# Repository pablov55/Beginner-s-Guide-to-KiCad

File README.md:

# Beginner's Guide to KiCad
###### _by: Pablo Villamejor_

This tutorial will walk you through a simple KiCad example project from schematic building to PCB layout. In this project we will be given a schematic plan to follow and construct from scratch. We'll also touch on library linking, editing, and creation. We'll also export our PCB's necessary fabrication outputs so the board can be manufactured.

Now to begin we must first download and install KiCad. Head over to [the download page of the KiCad website,](https://www.kicad.org/download/) select your operating system, and download the most recent model.

>[!IMPORTANT]
This tutorial was written using KiCad 8.0 on Windows 10. (i.e. Use this version to follow along.)

Once you install and open KiCad, you can go to _File, New Project,_ and then name it whatever you like. Once named, you may select __Schematic Editor__ to begin.

## Creating the Schematic
When opened, the __Schematic Editor__ should appear like this, plain and empty besides the red border and text boxes.  

The objective of this project is to recreate this simple circuit and prepare it for manufacturing. The example has only 6 major components which will make this task more simple than most, but it is sufficient in order to understand the fundamental steps of KiCad and PCB design.

### Adding Symbols

To begin recreating this circuit, first add the components. This can be done using the _Add Symbols_ button on the right toolbar, or press the _"A"_ button on your keyboard, then left click anywhere on your workspace to begin selecting your component.

This will open up a window where you can input the name of the component you are trying to place. Most of the components have their names beside them (unless they were renamed, like is the case for the connectors in the example circuit) or use common electronic symbols which make them easy to recognize. When you have the part selected you can rotate it using the _"R"_ button on your keyboard then left click again on your workspace to place it. You can also use the _"X"_ and _"Y"_ keys to rotate it along the X or Y direction respectively. After you place a component, you'll notice you're still in placement mode. Hit the _"esc"_ button on your keyboard to return to normal pointer mode. This works for all placement modes in KiCad so if you are confused you can always click _"esc"_ to return to the normal mode

>[!TIP]
When placing any symbol, KiCad will automatically annotate it based on the order you placed them. These annotations are key to remaining organized when building and assembling the PCB. You can change the annotations by double clicking them and inputting it manually, this can be done at any time. There is no standard on how annotations should be done, it varies from designer to designer, but try to follow a simple system in your annotations to avoid confusion for you and future viewers of your work.

This example circuit uses one transistor, two resistors, and three 1x2 female connectors. Place all the components somewhat centrally to the workspace and similar to how they appear in the example. Once you have them all on the workspace you are ready to move on to the next step which is adding the reference grounds.

### Placing Power Symbols

The process is the same as adding in the components however, instead of selecting the _"Add Symbols"_ button, you select the _"Add Power Symbols"_ button underneath it, or use the _"P"_ button on your keyboard. 

This will open up a similar window where you can search for the reference grounds. This window allows you to input all kinds of grounds, power sources, and various other power related symbols. When you've placed one down, you do not need to follow the same process for the rest of them. You may simply copy the component by clicking it and pressing _"ctrl + c"_ or hovering over it and pressing _"C"_ on your keyboard. Then pasting with _"ctrl + v"_

### Wiring the Schematic
Once you have all four ground references placed, you are ready to begin wiring the components. You can begin this by pressing the _"Add a Wire"_ button on your right toolbar, or press the _"W"_ button on your keyboard. Then simply left click on the component connectors, creating the necessary connections, and following the example circuit.

When you are done wiring, the circuit is functionally the same as the example. Now we just need to rename the various input terminals. This wont affect the functionality of the circuit, it is just a good industry practice to name your components for and future viewers of your schematics. As you can see from the image above I have already renamed my connectors, to do this you need to simply double click on the name of the component, or press the _"V"_ button on your keyboard while hovering over the component. This will open a window where you can input whatever name you'd like to give to the component.

### Running an Electrical Rules Check
Congratulations! If you finished up to here then you have successfully recreated the circuit in your _Schematic Editor_. The next step is to run an _Electrical Rules CHECK_ or _ERC_. This can be found on the upper toolbar on the right hand side. This just checks if the circuit you created follows all the basic electrical rules. It is basically a way to check if you forgotten anything important.

When ran the ERC reveals one error, as shown in the image above. This is a simple error basically saying that KiCad is can not distinguish which connector is the power input. You, the designer, knows which is the power input as you labelled the connector "POWER" but KiCad does not. This can be fixed by simply placing a Power Flag on the wire connecting the power input connector and its ground reference. The power flag can be found in the _"Add Power Symbols"_ window as the first result when you type "flag". You will know if you done it right if whe  your run the ERC again it will show no errors. 

### Assigning Footprints

We are almost done with the schematic editor, now we must assign the 3-Dimensional footprints to the symbols of the components. This will allow us to move on to the PCB editing. Footprints basically tell KiCad the exact dimensions of the real world component so that you may precisely pick where on your PCB board each component goes. 
To begin selecting the footprints, press the _"Run Footprint Assignment Tool"_ on the top toolbar. This will open up a window showing all the footprint libraries that KiCad has automatically installed on the left, the components in your schematic in the middle, and the applicable footprints for the chosen schematic on the right. 

As you can see in the image above, I already assigned the footprints to the symbols. Some of the components had footprints automatically selected; you do not have to edit those unless you have a specific version in mind. Footprints are usually provided by the real world component supplier. That is why there are so many different footprints for each schematic as different manufacturers provide slightly different products. When picking a footprint, you must make sure that the version you are picking is readily available for purchase and can meet your supply needs. Senior designers will know which electronics brands and manufacturers create the best components when choosing footprints. There are many different factors when selecting footprints, and is something that requires experience to develop. For now you may simply select the footprints I selected by searching their names in the search bar. 

>[!TIP]
 You can right-click any footprint and select "view selected footprint" to see how the footprint looks. You can then click the "Show 3D Viewer" on the top toolbar, or press "Alt + 3" to view the 3D rendered view of the component.

## PCB Editor

With the schematic completed and the footprints assigned, we can move on to designing the PCB itself. You can move on from the schematic editor to the PCB editor by pressing the _"Open PCB in Board Editor"_ on the top toolbar on the right side. Or you can simply return to the main KiCad window and select _"PCB Editor"_. __Don't forget to save the schematic editor file first!__

When you open up the board editor you will be greeted by this screen. To import the components from the schematic we just created, you need to press the _"Update PCB with changes made to the schematic"_ button on the top toolbar on the right side, or by simply pressing _"F8"_ on your keyboard. This button will automatically import the components allowing you to place them all at once. This button also automatically creates a netlist as this step used to have to be done manually in earlier KiCad versions.

 >[!NOTE]
 The netlist contains information regarding components, their designators, pins, and the names of any nets that connect each pin to components. Manufacturers may require this file for assembly. How to export this file, along with other files needed for PCB manufacturing, will be discussed near the end of the tutorial.

### PCB Setup

The _"Update PCB with changes made to the schematic"_ button can be pressed at any point in the editing process so don't be afraid to go back and change the schematic if you uncover issues. Because of that, before you place the components its always a good idea to set up your PCB by pressing the _"Edit Board setup"_ button on the top toolbar on the left.

In the PCB setup editor, you can change the different layers in the PCB. You can select which layers you need for specific projects. You can edit many different aspects and tools for the editor, most are technical while some are purely aesthetic.

One of the more important things to edit is the design rules, more specifically the constraints. These are usually set by manufacturers and can make or break the PCB design. Its always good to copy the values for each of these parameters based on your chosen PCB manufacturer's recommendations __before__ starting PCB editing. Since this project is simply an example you can leave those as is.

Leave most of the PCB setup as is as they are not necessary changes for this project. The only thing you must add is some _Pre-defined track sizes_. Go to the _"Pre-defined Sizes"_ tab and place a 0.3mm and a 0.5mm track size using the plus sign on the button. Tracks are the equivalent of wires in PCB editing so this gives us two set sizes to work with. 0.3mm for basic components and 0.5mm for any power related component. These sizes are not standards and should not be followed in every project, they are simply common and versatile track sizes that may come in handy during later steps. Once that is completed you may click ok.  
 __*When all your setup is complete you may now press F8, then press "Update PCB", and place your components somewhat centrally*__

### Arranging Footprints
When you place them down you'll see they all are imported in a pile which can be a little messy. Now you can see why annotations are important for organization. You can move the components by clicking and dragging them to place where you'd like. You can also hover over the component and press _"M"_ on your keyboard.  

>[!TIP]
You can hide the F.Fab and B.Fab layers by looking for them on the layer list on the right and clicking the eye symbol. These fabrication layers don't add too much information and hiding them makes the board less cluttered.

>[!TIP]
If you have two monitors, or you are adept at switching through tabs, you can select the part you wish to edit on your Schematic editor by clicking it and it will be selected as well in the PCB editor. This helps a ton in more complex projects.

When moving them you will see a sort of web or net connecting the components. This is to show you exactly where each component is supposed to be connected to. This will show were you are supposed to route the tracks _(connect the wires)_. Try and place the components in a way that makes the webs line up to where they are supposed to be connected. Try and make it so tracks are relatively direct and do not cross with each other, while the components are not too far spread. There are many, many, rules when it comes to component placing on a PCB; too many rules to go over in this tutorial. Many of these you will learn over time so for now just place them in a way that seems logical to you as this is just practice. 

>[!TIP]
Its good practice to start with the most crucial components then work your way down.

As you can see I placed the components so that the tracks do not run through anything too important. The only web that runs through a component is the reference ground of __J2__ but that is ok since we will not route the grounds in this project.  

    Tip : You can press "Alt + 3" at any point in this editor to view the 3D model of your design. As you can see in the image below the components mimic the placement on the editor.

### Adding Board Outline
As you can see in the 3D editor and error appears that says _"Board outline is missing"_. That is simply because we have not set the board cut out size yet. To add that, first select the _"Edge.Cuts"_ layer in your layer list on the right. You will know its selected if a blue arrow appears next to the layer. 

We will be drawing lines in this layer to designate the board cut offs. This will set the board size for manufacturing. It is good practice to go for whole number sizes. For this project I am going for a 25mmx20mm board. To bring out the measuring tool you can press _"Ctrl + Shift + M"_

>[!TIP]
You can press the "N" button on your keyboard to change the grid size for greater accuracy. I recommend a grid size of 1mm for edge cutting.

To draw the line, select the _"Draw a Line"_ tool on the right tool bar. Then draw the lines as an outline to the PCB. Feel free to move around the components so that they fit better, nothing is set in stone at this point. If you want curved edges you can use the arc tool under the line tool to create arcs on the edges. 

When finished, it should look something like this. The curved edges are optional so if yours are straight then that is fine. 

As you can see in the 3D viewer, The board cuts worked and KiCad now knows the shape our board will be.

### Routing the Components

Nice we have a rough layout formed, we can begin routing. This is usually the most tedious step that requires the most precision. However since our circuit is very simple, this process will not be too difficult. 

To begin, I like adding a copper ground plane. This makes it so we do not have to route any reference grounds, and it makes routing regular grounds easier as well.   
To do this, we need to first select the bottom copper layer (_"B.Cu"_ on your layer list), then click the _"Add filled Zone"_ button on your right toolbar. 

After pressing, this window will pop up. Select the GNDREF as that is what we want this plane to link. The clearances and widths for filled zones differ for different applications, but for this application you may simply change the clearance to 0.3mm. 

Once you set the various properties of the filled zone, you will be moved to drawing mode. Encompass your entire PCB in this drawing as shown in the picture above. Once the box is closed, you can press the _"B"_ key on your keyboard to fill the zone. This creates the bottom copper layer and is visible in the 3D viewer. 

>[!TIP]
You can hide the blue box by pressing the "Show only zone boundaries" on the left toolbar near the bottom. This makes routing so much easier on the eyes.

The square holes usually indicate grounds in the industry so you can see that all our reference grounds no longer need to be routed. This makes future routing of non-reference grounds much easier since you can just punch a hole in the board (Press _"V"_ while the routing a ground). However since this design only uses reference grounds, we are finished routing the ground.

Next we will be routing the regular components. Its always a good rule of thumb to start at the most critical components. To start, simply press the _"Route Tracks"_ button on the right toolbar or the _"X"_ button on your keyboard. Click the portion of the component that the route needs to attach to, then trace the track towards the component it should connect to. You can always delete the tracks by selecting them and clicking _backspace_ or _delete_ or undo with   
_ctrl + z_  
 _Don't forget, 0.3mm for non-power related components!_

Its good practice to instantly move away from the component as you place the tracks. This makes more space for other tracks as the more space between tracks the less likely you'll experience an error later on. Just follow the net as to where to connect the tracks.   
_Don't forget, 0.5mm for power related components!_

When you finished your routing your board will look similar to this. Since the circuit is so simple, none of the tracks are near each other so we didn't have to use any advanced techniques. Heres a simple tip, When routing a component you can click _"V"_. This drops the track one layer so that you can go underneath existing tracks. This is very important for mor complex designs. You can also see the tracks in the 3D viewer.

>[!TIP]
Move the silkscreen labels (J1, J2, Q1, ..etc.) out of the way of the tracks. These will be printed on the board and may be illegible if placed over a track.

### Running a Design Rules Check

Now that the routing is finished, you can run a _"Design Rules Check"_. This is similar to the electrical rules check of the schematic editor. It makes sure you didn't forget anything too obvious and checks your design against the constraints you set in the setup. 

You can find it on the top toolbar near the right side. Since we did not set any constraints at the start, and our circuit is simple, the check should come out like this with no errors. 

## Exporting Gerbers and Other Key Files

Once your DRC has come back with no errors or unconnected items, your PCB is basically ready for assembly! We now need to export the files to send to the PCB manufacturers. These files are usually the Gerber files, the drill files, the BOM, and the netlist. Some manufacturers require more and some require less but knowing how to export these files is important going forward. 

Simply go to _File_ then _Fabrication Outputs_ and select the files you need. Drill and Gerber files are the most critical files so start with those. I always do the drill files before the Gerber files

After selecting _"Drill Files"_ in _Fabrication Outputs_ you will be shown this screen. In this you can go into the specific of how you want this file created but we will not go into the details in this tutorial. You may research each of these options on your own but, for simplicity sake you may just use the defaults when Generating the files. Select the folder you want the files to be generated in and click the _"Generate Drill File"_ button

Once the drill files are generated, you can go and generate Gerber files. Same process as the Drill files, just select the _"Gerber Files"_ in _Fabrication Outputs_. In this window you will be able to pick which layers you want generated in the file as well as various other options. Again we will not go into the specifics, you can find resources on it all over the internet. For this practice simply input the target folder of these files and click _"Plot"_.

The bill of materials is a little different. You can just go to _Fabrication Outputs_ and download your BOM from their but we have not edited it yet. To do so you must go back to the _Schematic Editor_ and click the BOM button ont he top toolbar on the right side. This will open up the BOM editor where you can manually add the specific components you need for your device. When you finish editing it, you may press _Export_ to download the BOM file to the chosen folder.

## Viewing your Gerber files

KiCad has a built in Gerber viewer called __*Gerber Viewer*__ 

When opening it you will be greeted with this blank workspace. In order to open the Gerber files you just created you can go to _File_ then _Open Gerber Plot Files_ then go to the folder you selected they would be generated in and select all the files that end in _.gbr_

>[!TIP]
You can select multiple files by clicking the top Gerber file in the list then holding shift and clicking the bottom Gerber file.

When you load it up it should look like this. This shows what the manufacturer would receive to make your PCB. This is when you should do all your final checks to see any mistakes.

After loading up the Gerber files now you can go to _File_ then _"Open Excelon Drill Files"_ and select the drill file you just generated. You should see another layer get added as seen in the picture above. You can then start hiding layers to see every part of what you designed. 

Just click the check boxes on the right side layer list to hide the layers. This way you can double check every inch of your design. Once your satisfied with your design, you can send these files to a PCB manufacturer and have them made. Congratulations! With that you know all the basics of KiCad and PCB manufacturing.  

>[!IMPORTANT]
The guide isn't done just yet! Keep scrolling for some extra tips!

# Miscellaneous Tips
## Adding Symbol and Footprint Libraries

To edit your symbol or footprint libraries, you can got to _Preferences_ then select which you want to edit. The process is the same for both and are interchangeable. For this example, let us try adding a footprint library, but the steps are the same for symbols. 

To begin you need a library to upload to KiCad. You can find various kinds online, I'll leave it up to you as to what you want to add to your KiCad. In this example I will be adding the _Sparkfun-Capacitors_ Library. As you can see I already have other Sparkfun libraries installed.

Once you have the files you can click the plus button, then the folder symbol in the empty row that was created, then navigate to the file you want to add. You can then assign a name to it and click ok. If the format of the files was right, you should be able to use your new symbols in the schematic editor. 

Don't forget to do the same for the footprint library or you wont be able to find the right footprints for your symbols!

## Adding 3D models

Some footprints in the library are incomplete and do not have a 3D model. This is ok most of the time since it is not a requirement for assembly. You can design the entire PCB without using the 3D viewer; however, I think it helps you make informed decisions on components sizes and really helps the design process. If you want to add a 3D model to an incomplete footprint heres how!

As you can see in the example, the footprint works and is correct but the 3D view is missing minus the pinholes. To add a working 3D model for this, we need to find it online. Usually manufacturers will provide these models and are usually relatively easy to find.

To do this you need to first select the part in the _Schematic Editor_ then double click it and look for the part number. In the image above, the part number is the numbers highlighted. Usually they are listed at the end of the footprint file name. When this number is googled, it leads to the manufacturers website. The site has a downloads section with the exact CAD we need. Download the STP file.

Once you have the file place it somewhere you can easily find it, I moved mine to the project file.

.png>)

Once you have the file and you know where it is, you now need to double click on the footprint in the __PCB Editor__ and this window should show up. Select the _3D Models_ section and you should see the broken model.

You can delete the broken model with the trashcan icon under the list of models. You can then use the folder icon to select the file you just downloaded. It should appear something like this.

The model may need some scaling and offsetting to make it fit right. This particular model needed to be offset by 1mm in the Y and Z directions. This part may take some trial and error but when you get it right it will look perfect.

After clicking _Ok_ your footprint will have a working 3D model and will look right at place in your design!

## Creating Custom Footprints

In some cases you will need to use a part that does not have a library available online. In order to fix this we can create our own custom footprints and symbols. 

To start making a custom footprint, go over to the main KiCad launcher and press _"Footprint Editor"_. Once there you will be greeted with a blank document. First start by creating a custom library to put your footprint in. You can do this by going to _File_ then _New library_. Name it whatever you like and select _Global_ so that the footprint is available for all your future projects. Then you select the type of component you are making, in this example we will create a through hole type component.

In order to create a footprint, you need the precise measurements of the pad distances and the sizes. The image shown below is incomplete and missing some crucial data but you can always find what you need with a pair of calipers. In creating the footprint we need to be as precise as possible. 

To begin, first find the distance between pads of the component you are trying to create. In my case, the space is 2.54mm. In order to precisely place these pads, we need to make use of the grid. Lucky for me there is a default 2.54mm grid which made my pad placing a lot easier. If the space between your pads is not found on the grid list, you may create a custom grid by clicking the drop down arrow of the grid selector then pressing _Edit Grids_. This will open up a window where you can press the plus sign to create you own custom grid.

Now we move on to pad placement. To start select the _"Add a pad"_ button on the right toolbar on the top side. Then place the pads following your grid so that they are properly spaced. Make sure your in the Front silkscreen layer!. Once you placed one row of pads you can copy and paste them all to the other side. Make sure the measurements remain precise!

>[!TIP]
Don't forget you can use the measurement tool!

But wait! Before you copy and paste the entire row of pads, you can select them by double clicking the symbol. This way you can edit the pad number/name __(very important)__ as well as pad sizes, clearances, and many other variables. Make sure these settings match that of you component. Make sure the pins are properly spaced and size is accurate before copying it to the other side. 

Next we will create the silkscreen outline. This makes it so an outline will be traced in the PCB for easier assembly. Its good to make this one slightly larger than the actual dimensions so that it is still slightly visible after mounting the component. 

Since this step is not the most necessary, some footprints don't even have it, you do not have to be so accurate with this one. Try to make it look right so that the assemblers have an easier time and less mistakes are made. Once you finished with that you have a finished footprint ready for use!

## Creating Custom Symbols

Now that we have our footprint ready, we can move on to creating our symbol! Unlike footprints, symbols do not have to be precise at all. You have full control over the aesthetics and the look of the symbol you are creating. When I create custom symbols I try to mimic the shape of the actual component but some prefer to use the electronic symbols. To begin making your symbol first go to the main KiCad launcher and press the _"Symbol Editor"_. Then same as with the footprint, we must first create a new library to place it in. 

Once you have your new library, press the _"Create new symbol"_ button on the top toolbar or under the _Files_ tab. 

Here you will be given the options to change various details about the symbol. These options are not the most important; you may just input the name and choose a reference symbol while leaving the rest default. 

Since the component I'm making is a rectangular micro controller, I used the rectangle tool on the right toolbar to create it. As I said previously, this step is not the most precise so you may use any shape you would like. KiCad has tools to create free lines and arcs so that you may create any shape you really desire. When you have a closed shape, you may double click it to open its properties menu.  Simply select _"Fill with body background color"_. This will fill in the shape and tell KiCad that this is the main body of the symbol. 

Once your body is filled, you may begin placing the various pins for the component. The _"Add pins"_ tool is found on the right toolbar near the top. When you have the tool selected and you click on the work surface, you will be greeted with this window. With it you can change various things about the pins. This step is the most crucial part of creating KiCad symbols. You need to make sure the type of pins you use are correct and correctly labeled as well. You can usually find the pin configurations of components online; you may use them as guides in this step. 

>[!TIP]
You can edit symbols at anytime during any project so do not be afraid to make mistakes here as you can always fix them later. 

I attached all the pins on one side before moving on to the next. Some pins had names while others had numbers. 

Once you have both sides fully pinned and you added all the parts you needed, you are basically done! This symbol is ready for use in the schematic editor but it has no footprint assigned to it yet. To do this, go to the _"Edit symbol properties"_ button on the top toolbar. From there you can go to the assigned footprint and browse through your footprint libraries. When there, select the footprint you just created to assign it to the symbol.

Afterwards you can press "ok" and that will give your symbol a default footprint!

With that your symbol is complete and ready to be used in a schematic!

## Resources and going further

Congratulations! With that yu have completed the tutorial! Now you know the basics of KiCad and can begin your journey creating PCBs and various projects. Have fun!

If your looking for more information on KiCad or you want to learn more than the basics I highly recommend watching tutorials online. There are many amazing guides out there that can show you all the features and capabilities of KiCad as well as PCB design as a whole. 

[Phil's Lab](https://www.youtube.com/@PhilsLab/videos) is a great youtube channel to learn more on these topics for free. He covers all the basics of PCB design and gives helpful tips and information he gained from years of working in the industry. He has multiple KiCad tutorials you can follow along with as well as real world electronics projects. He also has a bunch of courses you can take [here](https://fedevel.com/instructors/philip-salmony#courses) which go into greater detail, however some require payment. 

This guide was based off this old [SparkFun guide.](https://learn.sparkfun.com/tutorials/beginners-guide-to-kicad/all) It was made on an older version of KiCad and needed some updates which is why this tutorial was made. Despite its age, it still contains tons of information on KiCad and gives tons of tips. They also have a wide range of resources on the site that you can use to learn more.

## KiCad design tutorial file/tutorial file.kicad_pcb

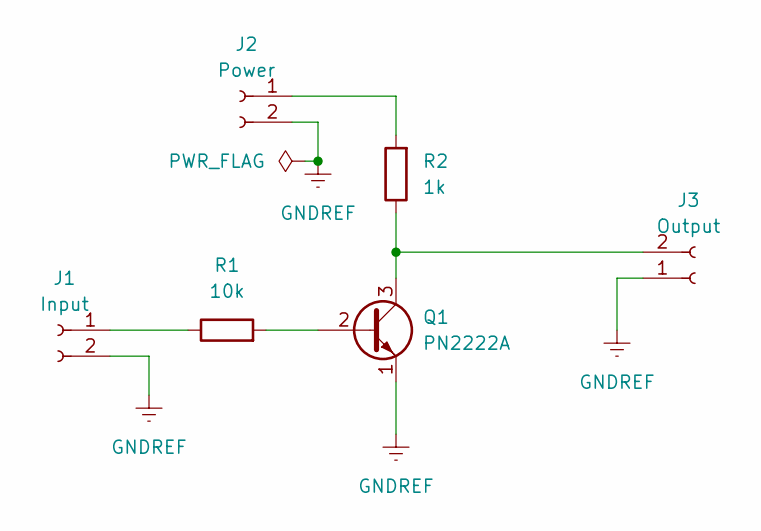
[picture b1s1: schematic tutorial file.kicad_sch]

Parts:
J1: Input; PinSocket_1x02_P1.27mm_Vertical
J2: Power; PinSocket_1x02_P1.27mm_Vertical
J3: Output; PinSocket_1x02_P1.27mm_Vertical
Q1: PN2222A; TO-92_Inline
R1: 10k; R_0603_1608Metric
R2: 1k; R_0603_1608Metric

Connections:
GNDREF: J1.2, J2.2, J3.1, Q1.1 (E)
unnamed: J1.1, R1.1
unnamed: J2.1, R2.2
unnamed: J3.2, Q1.3 (C), R2.1
unnamed: Q1.2 (B), R1.2

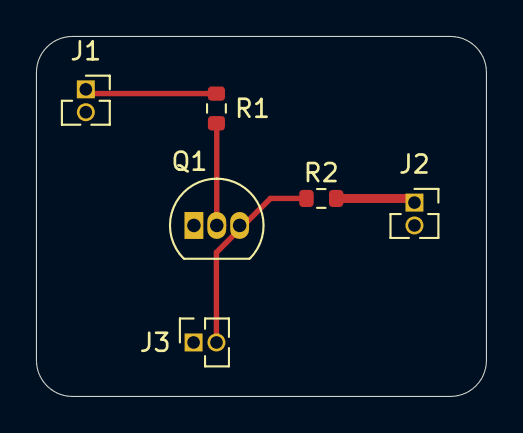
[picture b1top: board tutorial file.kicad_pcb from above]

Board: 2 copper layers, 25.0 x 20.0 mm, 6 parts (0 on the bottom side), 5 nets.

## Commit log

2024-04-08 "first"
2024-04-08 Added README
2024-04-08 Added pictures!
